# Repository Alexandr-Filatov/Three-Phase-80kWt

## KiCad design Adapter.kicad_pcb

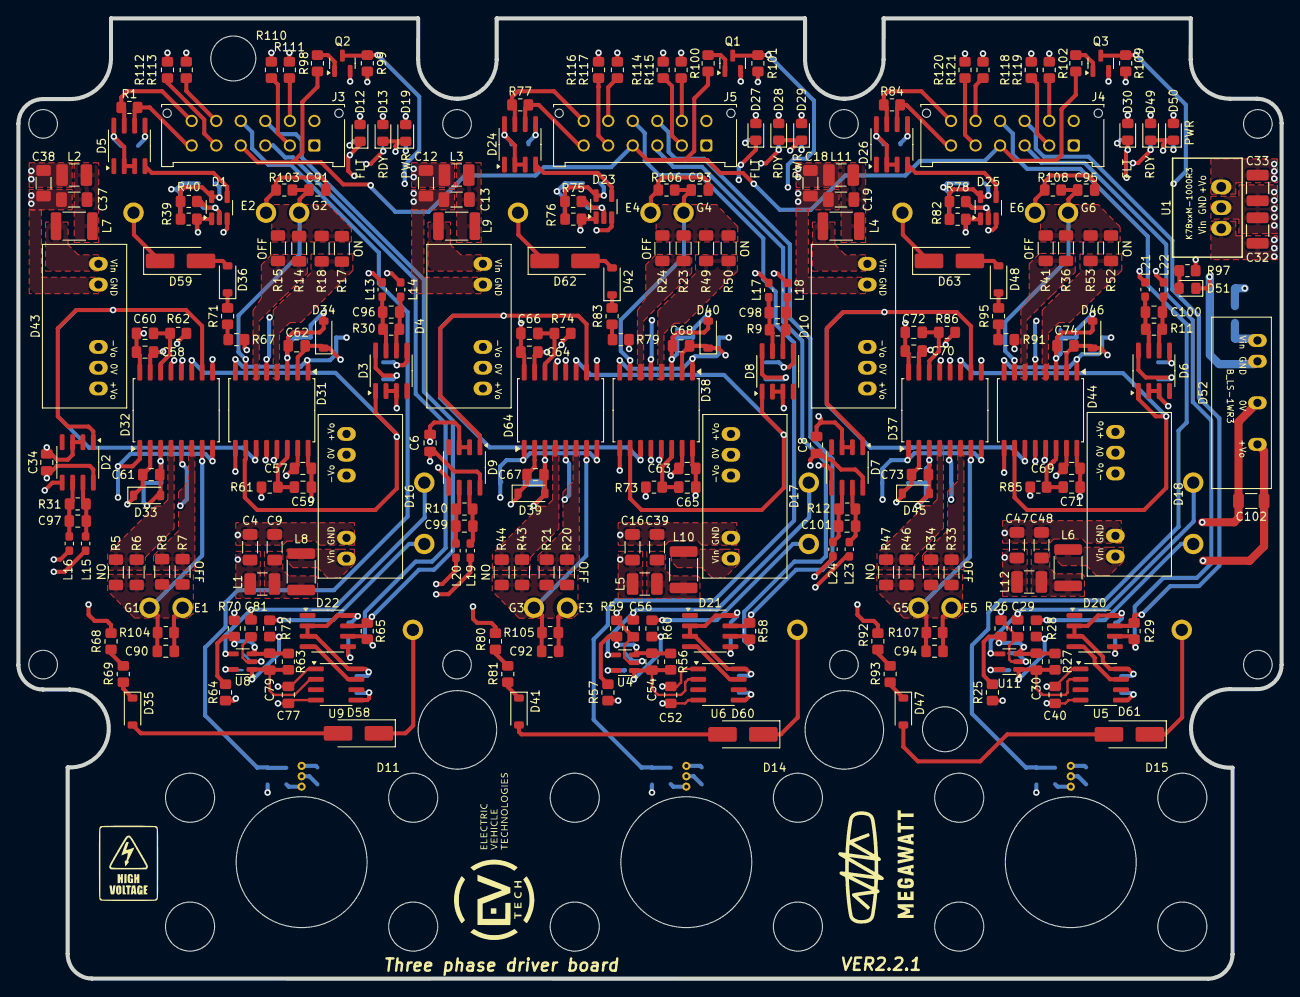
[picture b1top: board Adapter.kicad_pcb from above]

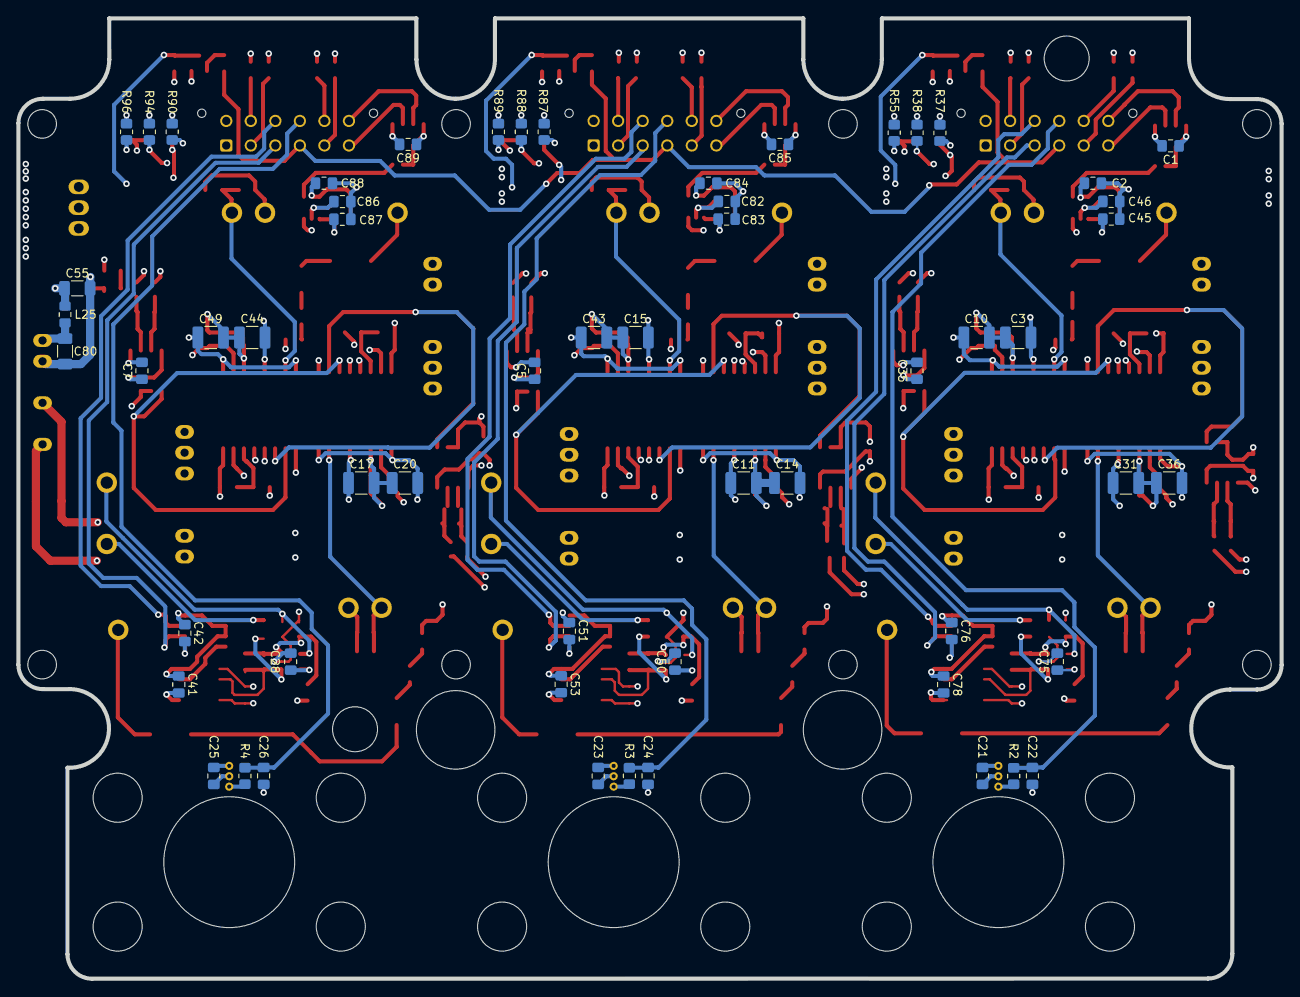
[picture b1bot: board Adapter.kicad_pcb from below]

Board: 6 copper layers, 154.4 x 117.4 mm, 308 parts (57 on the bottom side), 179 nets.

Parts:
C1, C2, C5, C6, C7, C8, C28, C34, C35, C40, C41, C42, C50, C51, C52, C53, C75, C76, C77, C78, C84, C85, C88, C89: 2.2u; C_0805_2012Metric_Pad1.18x1.45mm_HandSolder
C3, C10, C11, C14, C15, C17, C20, C31, C32, C36, C43, C44, C49: 10u; C_1210_3225Metric_Pad1.33x2.70mm_HandSolder
C4, C9, C12, C13, C16, C18, C19, C37, C38, C39, C47, C48, C55, C80: 4.7u; C_1206_3216Metric_Pad1.33x1.80mm_HandSolder
C21, C23, C25, C57, C58, C63, C64, C69, C70: 0.1u; C_0805_2012Metric_Pad1.18x1.45mm_HandSolder
C22, C24, C26: 10u; C_0805_2012Metric_Pad1.18x1.45mm_HandSolder
C29, C56, C81: 1n; C_0805_2012Metric_Pad1.18x1.45mm_HandSolder
C30, C45, C46, C54, C59, C60, C65, C66, C71, C72, C79, C82, C83, C86, C87, C96, C97, C98, C99, C100, C101: 56p; C_0805_2012Metric_Pad1.18x1.45mm_HandSolder
C33: 22u; C_1210_3225Metric_Pad1.33x2.70mm_HandSolder
C61, C62, C67, C68, C73, C74: 100p; C_0805_2012Metric_Pad1.18x1.45mm_HandSolder
C90, C91, C92, C93, C94, C95: C_0805_2012Metric_Pad1.18x1.45mm_HandSolder
C102: 10u; C_1206_3216Metric_Pad1.33x1.80mm_HandSolder
D1, D23, D25: SOT-23-5_HandSoldering
D2, D3, D5, D6, D7, D8, D9, D20, D21, D22, D24, D26: SOIC-8_3.9x4.9mm_P1.27mm
D4, D10, D16, D17, D18, D43: QA
D11, D14, D15: YMC15S-500A
D12, D13, D19, D27, D28, D29, D30, D49, D50, D51: LED_0805_2012Metric_Pad1.15x1.40mm_HandSolder
D31, D32, D37, D38, D44, D64: SOIC-16W_7.5x10.3mm_P1.27mm
D33, D34, D35, D36, D39, D40, D41, D42, D45, D46, D47, D48: D_SOD-123
D52: B_LS-1WR3
D58, D59, D60, D61, D62, D63: D_SMA_Handsoldering
J1: GD820HTX75P6HB
J3, J4, J5: Molex_Micro-Fit_3.0_43045-1212_2x06_P3.00mm_Vertical
L1, L2, L3, L5, L11, L12: 12u; L_1210_3225Metric_Pad1.42x2.65mm_HandSolder
L4, L6, L7, L8, L9, L10: 47u; L_1812_4532Metric_Pad1.30x3.40mm_HandSolder
L13, L14, L15, L16, L17, L18, L19, L20, L21, L22, L23, L24: 1u; L_0603_1608Metric_Pad1.05x0.95mm_HandSolder
L25: 6.8u; L_0805_2012Metric_Pad1.15x1.40mm_HandSolder
Q1, Q2, Q3: SOT-23
R1, R9, R10, R11, R12, R29, R30, R31, R58, R61, R62, R65, R73, R74, R77, R84, R85, R86: 120; R_0805_2012Metric_Pad1.20x1.40mm_HandSolder
R2, R3, R4, R69, R71, R81, R83, R93, R95: 0; R_0805_2012Metric_Pad1.20x1.40mm_HandSolder
R5, R6, R17, R18, R43, R44, R46, R47, R49, R50, R52, R53: 6.8; R_1206_3216Metric_Pad1.30x1.75mm_HandSolder
R7, R8, R14, R15, R20, R21, R23, R24, R33, R34, R36, R41: 10; R_1206_3216Metric_Pad1.30x1.75mm_HandSolder
R25, R26, R27, R56, R57, R59, R63, R64, R70, R103, R104, R105, R106, R107, R108: 10k; R_0805_2012Metric_Pad1.20x1.40mm_HandSolder
R28, R60, R72: 2.2k; R_0805_2012Metric_Pad1.20x1.40mm_HandSolder
R37, R38, R39, R40, R75, R76, R78, R82, R87, R88, R90, R94, R97, R99, R101, R109: 1k; R_0805_2012Metric_Pad1.20x1.40mm_HandSolder
R55, R89, R96: 3k; R_0805_2012Metric_Pad1.20x1.40mm_HandSolder
R67, R68, R79, R80, R91, R92: 2.4k; R_0805_2012Metric_Pad1.20x1.40mm_HandSolder
R98, R100, R102: 4.7k; R_0805_2012Metric_Pad1.20x1.40mm_HandSolder
R110, R111, R112, R113, R114, R115, R116, R117, R118, R119, R120, R121: 560; R_0805_2012Metric_Pad1.20x1.40mm_HandSolder
U1: K78xxM-1000R3
U4, U8, U11: SOT-23-5
U5, U6, U9: SOIC-8_3.9x4.9mm_P1.27mm

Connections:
+5V: C1.1, C2.1, C5.1, C6.1, C7.1, C8.1, C21.1, C23.1, C25.1, C33.1, C34.1, C35.1, C41.1, C42.1, C51.1, C53.1, C57.2, C58.2, C63.2, C64.2, C69.2, C70.2, C76.1, C78.1, C84.1, C85.1, C88.1, C89.1, D1.5 (Vcc), D2.8 (VCC), D3.8 (VCC), D5.2 (RE), D5.3 (DE), D5.8 (VCC), D6.8 (VCC), D7.8 (VCC), D8.8 (VCC), D9.8 (VCC), D11.1 (+Vcc), D14.1 (+Vcc), D15.1 (+Vcc), D20.2 (RE), D20.3 (DE), D20.8 (VCC), D21.2 (RE), D21.3 (DE), D21.8 (VCC), D22.2 (RE), D22.3 (DE), D22.8 (VCC), D23.5 (Vcc), D24.2 (RE), D24.3 (DE), D24.8 (VCC), D25.5 (Vcc), D26.2 (RE), D26.3 (DE), D26.8 (VCC), D31.15 (Vcc1), D32.15 (Vcc1), D37.15 (Vcc1), D38.15 (Vcc1), D44.15 (Vcc1), D64.15 (Vcc1), R37.2, R39.2, R40.2, R75.2, R76.2, R78.2, R82.2, R87.2, R90.2, R97.2, R99.2, R101.2, R109.2, R111.2, R113.2, R115.2, R117.2, R119.2, R121.2, U1.3 (+Vo), U5.8 (VDD2), U6.8 (VDD2), U9.8 (VDD2)
+5VA: C28.1, C40.1, C50.1, C52.1, C75.1, C77.1, C102.2, D52.6 (+Vo), R25.2, R57.2, R64.2, U4.5 (V+), U5.1 (VDD1), U6.1 (VDD1), U8.5 (V+), U9.1 (VDD1), U11.5 (V+)
+15V: C4.1, C12.1, C16.1, C18.1, C32.1, C38.1, C47.1, C55.1, J3.1, J4.1, J5.1, L1.1, L2.1, L3.1, L5.1, L11.1, L12.1, L25.1, R55.2, R89.2, R96.2, U1.1 (Vin)
+15V_H1: C31.1, D32.5 (Vcc2), D43.7 (+Vo)
+15V_H2: C11.1, D4.7 (+Vo), D64.5 (Vcc2)
+15V_H3: C17.1, D10.7 (+Vo), D37.5 (Vcc2)
+15V_L1: C3.1, D16.7 (+Vo), D31.5 (Vcc2)
+15V_L2: C15.1, D17.7 (+Vo), D38.5 (Vcc2)
+15V_L3: C44.1, D18.7 (+Vo), D44.5 (Vcc2)
-15V_H1: C36.2, D32.1 (Vee2), D32.8 (Vee2), D43.5 (-Vo)
-15V_H2: C14.2, D4.5 (-Vo), D64.1 (Vee2), D64.8 (Vee2)
-15V_H3: C20.2, D10.5 (-Vo), D37.1 (Vee2), D37.8 (Vee2)
-15V_L1: C10.2, D16.5 (-Vo), D31.1 (Vee2), D31.8 (Vee2)
-15V_L2: C43.2, D17.5 (-Vo), D38.1 (Vee2), D38.8 (Vee2)
-15V_L3: C49.2, D18.5 (-Vo), D44.1 (Vee2), D44.8 (Vee2)
C1: D58.1 (K), J1.1
C2: D59.1 (K), J1.2
C3: D60.1 (K), J1.9
C4: D62.1 (K), J1.10
C5: D61.1 (K), J1.17
C6: D63.1 (K), J1.18
Current_A_out: C22.1, J3.10, R2.2
Current_B_out: C24.1, J5.10, R3.2
Current_C_out: C26.1, J4.10, R4.2
E1: C31.2, C36.1, C61.2, C90.1, D32.3 (GND2), D33.2 (A), D43.6 (0V), J1.3, R104.1
E2: C3.2, C10.1, C62.2, C91.1, D16.6 (0V), D31.3 (GND2), D34.2 (A), J1.4, R103.1
E3: C11.2, C14.1, C67.2, C92.1, D4.6 (0V), D39.2 (A), D64.3 (GND2), J1.11, R105.1
E4: C15.2, C43.1, C68.2, C93.1, D17.6 (0V), D38.3 (GND2), D40.2 (A), J1.12, R106.1
E5: C17.2, C20.1, C73.2, C94.1, D10.6 (0V), D37.3 (GND2), D45.2 (A), J1.19, R107.1
E6: C44.2, C49.1, C74.2, C95.1, D18.6 (0V), D44.3 (GND2), D46.2 (A), J1.20, R108.1
ERR_A_N: D5.7 (B), J3.12, R1.1
ERR_A_P: D5.6 (A), J3.6, R1.2
ERR_B_N: D24.7 (B), J5.12, R77.1
ERR_B_P: D24.6 (A), J5.6, R77.2
ERR_C_N: D26.7 (B), J4.12, R84.1
ERR_C_P: D26.6 (A), J4.6, R84.2
FLT_A: C45.1, D1.1 (B), D12.1 (K), D31.13 (~FLT), D32.13 (~FLT), R39.1
FLT_B: C83.1, D23.1 (B), D27.1 (K), D38.13 (~FLT), D64.13 (~FLT), R76.1
FLT_C: C87.1, D25.1 (B), D30.1 (K), D37.13 (~FLT), D44.13 (~FLT), R82.1
G1: C90.2, D32.7 (CLAMP), J1.5, R5.1, R6.1, R7.2, R8.2, R104.2
G2: C91.2, D31.7 (CLAMP), J1.6, R14.2, R15.2, R17.1, R18.1, R103.2
G3: C92.2, D64.7 (CLAMP), J1.13, R20.2, R21.2, R43.1, R44.1, R105.2
G4: C93.2, D38.7 (CLAMP), J1.14, R23.2, R24.2, R49.1, R50.1, R106.2
G5: C94.2, D37.7 (CLAMP), J1.21, R33.2, R34.2, R46.1, R47.1, R107.2
G6: C95.2, D44.7 (CLAMP), J1.22, R36.2, R41.2, R52.1, R53.1, R108.2
GND: C1.2, C2.2, C4.2, C5.2, C6.2, C7.2, C8.2, C9.2, C12.2, C13.2, C16.2, C18.2, C19.2, C21.2, C22.2, C23.2, C24.2, C25.2, C26.2, C32.2, C33.2, C34.2, C35.2, C37.2, C38.2, C39.2, C41.2, C42.2, C45.2, C46.2, C47.2, C48.2, C51.2, C53.2, C55.2, C57.1, C58.1, C59.1, C60.1, C63.1, C64.1, C65.1, C66.1, C69.1, C70.1, C71.1, C72.1, C76.2, C78.2, C80.2, C82.2, C83.2, C84.2, C85.2, C86.2, C87.2, C88.2, C89.2, D1.3 (GND), D2.2 (RE), D2.3 (DE), D2.5 (GND), D3.2 (RE), D3.3 (DE), D3.5 (GND), D4.2 (GND), D5.5 (GND), D6.2 (RE), D6.3 (DE), D6.5 (GND), D7.2 (RE), D7.3 (DE), D7.5 (GND), D8.2 (RE), D8.3 (DE), D8.5 (GND), D9.2 (RE), D9.3 (DE), D9.5 (GND), D10.2 (GND), D11.2 (0V), D13.1 (K), D14.2 (0V), D15.2 (0V), D16.2 (GND), D17.2 (GND), D18.2 (GND), D19.1 (K), D20.5 (GND), D21.5 (GND), D22.5 (GND), D23.3 (GND), D24.5 (GND), D25.3 (GND), D26.5 (GND), D28.1 (K), D29.1 (K), D31.9 (GND1), D31.16 (TEST), D32.9 (GND1), D32.16 (TEST), D37.9 (GND1), D37.16 (TEST), D38.9 (GND1), D38.16 (TEST), D43.2 (GND), D44.9 (GND1), D44.16 (TEST), D49.1 (K), D50.1 (K), D51.1 (K), D52.2 (GND), D64.9 (GND1), D64.16 (TEST), J3.7, J4.7, J5.7, Q1.2 (E), Q2.2 (E), Q3.2 (E), R110.1, R112.1, R114.1, R116.1, R118.1, R120.1, U1.2 (GND), U5.5 (GND2), U6.5 (GND2), U9.5 (GND2)
GNDA: C28.2, C29.2, C40.2, C50.2, C52.2, C56.2, C75.2, C77.2, C81.2, C102.1, D52.4 (0V), R26.1, R59.1, R70.1, U4.2 (V-), U5.4 (GND1), U6.4 (GND1), U8.2 (V-), U9.4 (GND1), U11.2 (V-)
unnamed: C9.1, L1.2, L8.1
unnamed: C13.1, L3.2, L9.1
unnamed: C19.1, L4.1, L11.2
unnamed: C37.1, L2.2, L7.1
unnamed: C39.1, L5.2, L10.1
unnamed: C48.1, L6.1, L12.2
unnamed: D1.4 (Y), D5.4 (DI)
unnamed: C97.1, D2.6 (A), L16.1, R31.2
unnamed: C97.2, D2.7 (B), L15.2, R31.1
unnamed: C96.1, D3.6 (A), L14.1, R30.2
unnamed: C96.2, D3.7 (B), L13.2, R30.1
unnamed: D4.1 (Vin), L9.2
unnamed: C100.1, D6.6 (A), L22.1, R11.2
unnamed: C100.2, D6.7 (B), L21.2, R11.1
unnamed: C101.1, D7.6 (A), L24.1, R12.2
unnamed: C101.2, D7.7 (B), L23.2, R12.1
unnamed: C98.1, D8.6 (A), L18.1, R9.2
unnamed: C98.2, D8.7 (B), L17.2, R9.1
unnamed: C99.1, D9.6 (A), L20.1, R10.2
unnamed: C99.2, D9.7 (B), L19.2, R10.1
unnamed: D10.1 (Vin), L4.2
unnamed: D11.3 (Output), R2.1
unnamed: D12.2 (A), R37.1
unnamed: D13.2 (A), R38.1
unnamed: D14.3 (Output), R3.1
unnamed: D15.3 (Output), R4.1
unnamed: D16.1 (Vin), L8.2
unnamed: D17.1 (Vin), L10.2
unnamed: D18.1 (Vin), L6.2
unnamed: D19.2 (A), R55.1
unnamed: D20.4 (DI), U5.7 (VOA)
unnamed: D21.4 (DI), U6.7 (VOA)
unnamed: D22.4 (DI), U9.7 (VOA)
unnamed: D23.4 (Y), D24.4 (DI)
unnamed: D25.4 (Y), D26.4 (DI)
unnamed: D27.2 (A), R87.1
unnamed: D28.2 (A), R88.1
unnamed: D29.2 (A), R89.1
unnamed: D30.2 (A), R90.1
unnamed: C62.1, D31.2 (DESAT), D34.1 (K), R67.2
unnamed: D31.4 (OUTH), R17.2, R18.2
unnamed: D31.6 (OUTL), R14.1, R15.1
unnamed: C59.2, D31.14 (~RST), R61.2
unnamed: C61.1, D32.2 (DESAT), D33.1 (K), R68.2
unnamed: D32.4 (OUTH), R5.2, R6.2
unnamed: D32.6 (OUTL), R7.1, R8.1
unnamed: C60.2, D32.14 (~RST), R62.2
unnamed: D35.2 (A), D58.2 (A)
unnamed: D35.1 (K), R69.1
unnamed: D36.2 (A), D59.2 (A)
unnamed: D36.1 (K), R71.1
unnamed: C73.1, D37.2 (DESAT), D45.1 (K), R92.2
unnamed: D37.4 (OUTH), R46.2, R47.2
unnamed: D37.6 (OUTL), R33.1, R34.1
unnamed: C72.2, D37.14 (~RST), R86.2
unnamed: C68.1, D38.2 (DESAT), D40.1 (K), R79.2
unnamed: D38.4 (OUTH), R49.2, R50.2
unnamed: D38.6 (OUTL), R23.1, R24.1
unnamed: C65.2, D38.14 (~RST), R73.2
unnamed: C67.1, D39.1 (K), D64.2 (DESAT), R80.2
unnamed: D41.2 (A), D60.2 (A)
unnamed: D41.1 (K), R81.1
unnamed: D42.2 (A), D62.2 (A)
unnamed: D42.1 (K), R83.1
unnamed: D43.1 (Vin), L7.2
unnamed: C74.1, D44.2 (DESAT), D46.1 (K), R91.2
unnamed: D44.4 (OUTH), R52.2, R53.2
unnamed: D44.6 (OUTL), R36.1, R41.1
unnamed: C71.2, D44.14 (~RST), R85.2
unnamed: D47.2 (A), D61.2 (A)
unnamed: D47.1 (K), R93.1
unnamed: D48.2 (A), D63.2 (A)
unnamed: D48.1 (K), R95.1
unnamed: D49.2 (A), R94.1
unnamed: D50.2 (A), R96.1
unnamed: D51.2 (A), R97.1
unnamed: C80.1, D52.1 (Vin), L25.2
unnamed: D64.4 (OUTH), R43.2, R44.2
unnamed: D64.6 (OUTL), R20.1, R21.1
unnamed: C66.2, D64.14 (~RST), R74.2
unnamed: Q1.1 (B), R100.2
unnamed: Q2.1 (B), R98.2
unnamed: Q3.1 (B), R102.2
unnamed: R67.1, R71.2
unnamed: R68.1, R69.2
unnamed: R79.1, R83.2
unnamed: R80.1, R81.2
unnamed: R91.1, R95.2
unnamed: R92.1, R93.2
unnamed: C54.1, R56.1, R57.1, R59.2, U4.3 (+)
unnamed: C30.2, R27.2, R28.1, U5.2 (VIA), U11.1
unnamed: C54.2, R56.2, R60.1, U4.1, U6.2 (VIA)
unnamed: C79.1, R63.1, R64.1, R70.2, U8.3 (+)
unnamed: C79.2, R63.2, R72.1, U8.1, U9.2 (VIA)
unnamed: C30.1, R25.1, R26.2, R27.1, U11.3 (+)
PWM1_H_N: J3.5, L15.1, R112.2
PWM1_H_P: J3.11, L16.2, R113.1
PWM1_L_N: J3.2, L13.1, R110.2
PWM1_L_P: J3.8, L14.2, R111.1
PWM2_H_N: J5.5, L19.1, R116.2
PWM2_H_P: J5.11, L20.2, R117.1
PWM2_L_N: J5.2, L17.1, R114.2
PWM2_L_P: J5.8, L18.2, R115.1
PWM3_H_N: J4.5, L23.1, R120.2
PWM3_H_P: J4.11, L24.2, R121.1
PWM3_L_N: J4.2, L21.1, R118.2
PWM3_L_P: J4.8, L22.2, R119.1
PWM_H1: D2.1 (RO), D31.11 (IN-), D32.10 (IN+)
PWM_H2: D9.1 (RO), D38.11 (IN-), D64.10 (IN+)
PWM_H3: D7.1 (RO), D37.10 (IN+), D44.11 (IN-)
PWM_L1: D3.1 (RO), D31.10 (IN+), D32.11 (IN-)
PWM_L2: D8.1 (RO), D38.10 (IN+), D64.11 (IN-)
PWM_L3: D6.1 (RO), D37.11 (IN-), D44.10 (IN+)
RDY_A: C46.1, D1.2 (A), D31.12 (RDY), D32.12 (RDY), R38.2, R40.1
RDY_B: C82.1, D23.2 (A), D38.12 (RDY), D64.12 (RDY), R75.1, R88.2
RDY_C: C86.1, D25.2 (A), D37.12 (RDY), D44.12 (RDY), R78.1, R94.2
T1: C81.1, J1.7, U8.4 (-)
T2: J1.8, R72.2
T3: C56.1, J1.15, U4.4 (-)
T4: J1.16, R60.2
T5: C29.1, J1.23, U11.4 (-)
T6: J1.24, R28.2
Temp_A_N: D22.7 (B), J3.9, R65.1
Temp_A_P: D22.6 (A), J3.3, R65.2
Temp_B_N: D21.7 (B), J5.9, R58.1
Temp_B_P: D21.6 (A), J5.3, R58.2
Temp_C_N: D20.7 (B), J4.9, R29.1
Temp_C_P: D20.6 (A), J4.3, R29.2
~RST_A: Q2.3 (C), R61.1, R62.1, R99.1
~RST_B: Q1.3 (C), R73.1, R74.1, R101.1
~RST_C: Q3.3 (C), R85.1, R86.1, R109.1
~RST: J3.4, J4.4, J5.4, R98.1, R100.1, R102.1

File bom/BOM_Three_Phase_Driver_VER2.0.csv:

Reference	Value	Footprint	Qty	DNP	Описание	Аналог
C1,C2,C5,C6,C7,C8,C27,C28,C34,C35,C40,C41,C42,C50,C51,C52,C53,C55,C75,C76,C77,C78,C80,C84,C85,C88,C89	2.2u	Capacitor_SMD:C_0805_2012Metric_Pad1.18x1.45mm_HandSolder	27		Unpolarized capacitor, small symbol	
C3,C4,C9,C10,C11,C12,C13,C14,C15,C16,C17,C18,C19,C20,C31,C32,C36,C37,C38,C39,C43,C44,C47,C48,C49	10u	Capacitor_SMD:C_1210_3225Metric_Pad1.33x2.70mm_HandSolder	25		-- смешанные значения --	
C21,C23,C25,C57,C58,C63,C64,C69,C70	0.1u	Capacitor_SMD:C_0805_2012Metric_Pad1.18x1.45mm_HandSolder	9		Unpolarized capacitor, small symbol	
C22,C24,C26	10u	Capacitor_SMD:C_0805_2012Metric_Pad1.18x1.45mm_HandSolder	3		Unpolarized capacitor, small symbol	
C29,C56,C81	10n	Capacitor_SMD:C_0805_2012Metric_Pad1.18x1.45mm_HandSolder	3		Unpolarized capacitor, small symbol	
C30,C45,C46,C54,C59,C60,C65,C66,C71,C72,C79,C82,C83,C86,C87	56p	Capacitor_SMD:C_0805_2012Metric_Pad1.18x1.45mm_HandSolder	15		Unpolarized capacitor, small symbol	
C33	22u	Capacitor_SMD:C_1210_3225Metric_Pad1.33x2.70mm_HandSolder	1		Unpolarized capacitor, small symbol	
C61,C62,C67,C68,C73,C74	220p	Capacitor_SMD:C_0805_2012Metric_Pad1.18x1.45mm_HandSolder	6		Unpolarized capacitor, small symbol	
D1,D23,D25	SN74AHC1G08DBVR	Package_TO_SOT_SMD:SOT-23-5_HandSoldering	3			
D2,D3,D5,D6,D7,D8,D9,D20,D21,D22,D24,D26	ADM3485E	Package_SO:SOIC-8_3.9x4.9mm_P1.27mm	12			
D4,D10,D16,D17,D18,D43	WRA1215S-3WR2	Mornsun:WRA_S-3WR2	6			
D11,D14,D15	YMC15S-1000A	Sensors_My:YMC15S-500A	3		YMC15S-1000A	
D12,D27,D30	FLT	LED_SMD:LED_0805_2012Metric_Pad1.15x1.40mm_HandSolder	3		Light emitting diode, small symbol	
D13,D28,D49	RDY	LED_SMD:LED_0805_2012Metric_Pad1.15x1.40mm_HandSolder	3		Light emitting diode, small symbol	
D19,D29,D50	PWR	LED_SMD:LED_0805_2012Metric_Pad1.15x1.40mm_HandSolder	3		Light emitting diode, small symbol	
D31,D32,D37,D38,D44,D64	NSI6651ASC-DSWR	Package_SO:SOIC-16W_7.5x10.3mm_P1.27mm	6			
D33,D34,D39,D40,D45,D46	MMSZ5240B	Diode_SMD:D_SOD-123	6		Schottky diode, small symbol	
D35,D36,D41,D42,D47,D48,D58,D59,D60,D61,D62,D63	MURS160	Diode_SMD:D_SMA_Handsoldering	12		Diode, small symbol	
D51	+5V	LED_SMD:LED_0805_2012Metric_Pad1.15x1.40mm_HandSolder	1		Light emitting diode, small symbol	
J1	GD820HTX75P6HB	IGBT_Modul:GD820HTX75P6HB	1		Generic connector, single row, 01x24, script generated (kicad-library-utils/schlib/autogen/connector/)	
J3	Control_A	Connector_Molex:Molex_Micro-Fit_3.0_43045-1212_2x06_P3.00mm_Vertical	1		Generic connector, double row, 02x06, top/bottom pin numbering scheme (row 1: 1...pins_per_row, row2: pins_per_row+1 ... num_pins), script generated (kicad-library-utils/schlib/autogen/connector/)	
J4	Control_C	Connector_Molex:Molex_Micro-Fit_3.0_43045-1212_2x06_P3.00mm_Vertical	1		Generic connector, double row, 02x06, top/bottom pin numbering scheme (row 1: 1...pins_per_row, row2: pins_per_row+1 ... num_pins), script generated (kicad-library-utils/schlib/autogen/connector/)	
J5	Control_B	Connector_Molex:Molex_Micro-Fit_3.0_43045-1212_2x06_P3.00mm_Vertical	1		Generic connector, double row, 02x06, top/bottom pin numbering scheme (row 1: 1...pins_per_row, row2: pins_per_row+1 ... num_pins), script generated (kicad-library-utils/schlib/autogen/connector/)	
L1,L2,L3,L4,L5,L6	4.7u	Inductor_SMD:L_1812_4532Metric_Pad1.30x3.40mm_HandSolder	6		Inductor	
Q1,Q2,Q3	BC817	Package_TO_SOT_SMD:SOT-23	3		NPN transistor, base/emitter/collector	
R1,R9,R10,R11,R12,R29,R30,R31,R58,R61,R62,R65,R73,R74,R77,R84,R85,R86	120	Resistor_SMD:R_0805_2012Metric_Pad1.20x1.40mm_HandSolder	18		Resistor, small symbol	
R2,R3,R4,R69,R71,R81,R83,R93,R95	0	Resistor_SMD:R_0805_2012Metric_Pad1.20x1.40mm_HandSolder	9		Resistor, small symbol	
R5,R6,R7,R8,R13,R14,R15,R16,R17,R18,R19,R20,R21,R22,R23,R24,R32,R33,R34,R35,R36,R41,R42,R43,R44,R45,R46,R47,R48,R49,R50,R51,R52,R53,R54,R66	10	Resistor_SMD:R_1206_3216Metric_Pad1.30x1.75mm_HandSolder	36		Resistor, small symbol	
R25,R26,R27,R56,R57,R59,R63,R64,R70,R103,R104,R105,R106,R107,R108	10k	Resistor_SMD:R_0805_2012Metric_Pad1.20x1.40mm_HandSolder	15		Resistor, small symbol	
R28,R60,R72	2.2k	Resistor_SMD:R_0805_2012Metric_Pad1.20x1.40mm_HandSolder	3		Resistor, small symbol	
R37,R38,R39,R40,R75,R76,R78,R82,R87,R88,R90,R94,R97,R99,R101,R109	1k	Resistor_SMD:R_0805_2012Metric_Pad1.20x1.40mm_HandSolder	16		Resistor, small symbol	
R55,R89,R96	3k	Resistor_SMD:R_0805_2012Metric_Pad1.20x1.40mm_HandSolder	3		Resistor, small symbol	
R67,R68,R79,R80,R91,R92	1.1k	Resistor_SMD:R_0805_2012Metric_Pad1.20x1.40mm_HandSolder	6		Resistor, small symbol	
R98,R100,R102	4.7k	Resistor_SMD:R_0805_2012Metric_Pad1.20x1.40mm_HandSolder	3		Resistor, small symbol	
R110,R111,R112,R113,R114,R115,R116,R117,R118,R119,R120,R121	560	Resistor_SMD:R_0805_2012Metric_Pad1.20x1.40mm_HandSolder	12		Resistor, small symbol	
U1	K7805M-1000R3	DCDC_My:K78xxM-1000R3	1			
U2,U3,U7	LM1117GS-5.0	Package_TO_SOT_SMD:SOT-223	3			
U4,U8,U11	LMV7219M5X/NOPB	Package_TO_SOT_SMD:SOT-23-5	3		Single Low-Power High-Speed Push-Pull Output Comparator, SOT-23-5	
U5,U6,U9	ADuM1200AR	Package_SO:SOIC-8_3.9x4.9mm_P1.27mm	3		Dual-channel digital isolator, Bidirectional communication, 3V/5V level translation, SOIC-8	SCM3728ASA

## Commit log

2023-10-03 Тестовая версия
2024-01-16 Поменял компаратор на пушпульный
2024-01-16 Поменял драйвера на китайские
2024-08-29 Zero commit
2024-09-02 Изменил схему
2024-09-05 Разместил все три стойки в своей области
2024-09-12 Добавил температурные контуры звщиты
2024-09-17 Убрал питание 3.3В
2024-09-23 Развел стойку фазы А
2024-09-25 Начал разводить вторую стойку
2024-09-26 Добавил новые разъёмы
2024-10-03 Развел вторую стойку
2024-10-06 Развел все
2024-10-08 REV2.0
2024-10-23 Отправил на проверку в резонит: изменил BOM
2024-10-24 Изменения: обновил BOM и названия в схеме
2024-10-24 Изменения: в BOM добавил столбец наличия компонентов
2024-11-12 Исправления: исправил нумерацию ножек датчиков тока
2024-11-12 Исправления: исправил номиналы подтяжек и сопротивления светодиодов
2024-11-12 Исправления: заменил полевые на биполярные в контуре RESET и изменил номиналы резисторов базы, исправил BOM
2024-11-13 Изменения: добавил подтяжки шины RS485
2024-11-17 VER2.0: отпаравил файлы в китай, обновил BOM
2024-11-19 Изменения: изменил BOM, сделал заказ
2024-11-27 Изменения: добавил папку Docs
2025-02-10 Изменения: поменял трассировку полигонов, изменил трассировку цепи DESAT в фазе А
2025-03-02 VER2.1 init
2025-03-03 VER2.1: переработал цепь DESAT
2025-03-11 VER2.1: отправил в резонит
2025-03-20 VER2.1: начал формировать закупку
2025-03-21 VER2.1: подправил BOM
2025-05-15 VER2.1: добавил монтажную схему
2025-05-21 VER2.1: добавил схему в доки
2025-05-25 VER2.2: начал менять источники питания драйверов
2025-05-29 VER2.2: удалил лишний затворный резистор
2025-06-03 VER2.2: все изменения в списке изменений
2025-06-04 VER2.2: добавил фильтры на вход ШИМа и обновил все доки
2025-06-04 VER2.2: пересохранил проект
2025-06-20 VER2.1: добавил СБ и 3D модели в доки
2025-06-25 VER2.2: сделал зазоры от коллекторов и эмитеров 3мм
2025-06-26 VER2.2: сделал полигоны нормально
2025-06-27 VER2.1: добавил всю документацию
2025-06-27 VER2.2: сделал изоллированное питание для температурных контуров
2025-06-27 VER2.2: переразвел доорожки
2025-06-30 VER2.2: доработал мелкие недостатки, оптимизировал дорожки и полигоны
2025-06-30 VER2.2: отправил в резонит
2025-06-30 VER3.0: начал расстановку
2025-07-04 VER2.1: нужно уменьшить вес линий размерных в СБ
2025-07-09 VER2.1: изменил вес линий в СБ
2025-07-09 VER2.1: переделал схему в один лист красиво
2025-07-10 VER2.1: исправил Э3 еще раз
2025-07-14 VER2.1: исправил СБ
2025-07-14 VER2.1: исправил Э3
2025-07-14 VER2.1: изменил название Э3
2025-07-16 VER2.1: сделал спецификацию и оформил BOM
2025-07-16 VER2.1: исправил BOM
2025-07-16 VER2.1: исправил спеку
2025-07-16 VER2.1: исправил спеку еще раз дважды
2025-07-17 VER2.2: обновил BOM, добавил лист закупки
2025-07-17 VER2.2: дозакупил на один комплект
2025-07-29 VER2.2: добавил монтажную схему
2025-08-01 VER2.1: добавил папку Drawings и добавил чертежи на модуль фаз
2025-08-01 VER2.1: улучшил спеку
2025-08-21 VER2.2.1: исправил косяк с питанием NTC, изменил номиналы затворов и цепи NTC
2025-08-25 VER2.2.1: создал папку для производственных доков
2025-08-25 VER2.2.1: собрал архив для производства в китае
2025-11-12 VER2.2.1: добавил папку с чертежами
2025-11-12 VER2.2.1: внес изменение в чертежи и добавил в папку доки
2025-11-12 VER2.2.1: исправил все доки
2025-11-14 VER2.2: исправил ошибки в доках
2025-11-19 VER2.2.1: убрал линию со схемы
2025-11-19 VER2.2.1: переименовал схему
2025-11-20 VER2.2.1: исправил сборочный чертеж
